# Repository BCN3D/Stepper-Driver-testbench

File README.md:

# Stepper Driver Test Bench
Electronics Test Bench used for testing and callibrating the Stepper drivers for the BCN3D Sigma.
It's based on a Pogo bed system where the bottom board has the components and the other two boards serve as support for
the board to test (Stepper driver).

Basically it's made for callibrating the power of the DRV8825 based Stepper drivers used in the BCND3D Sigma and testing them out
with a real motor.

It uses capacitive touch sensor instead of mechanical switches as it will be used a lot...
We were inspired by the awesome tutorial by [Sparkfun](https://learn.sparkfun.com/tutorials/constant-innovation-in-quality-control?_ga=1.225836058.1496890805.1425539418)

##Code
Implements the [AccelStepper](http://www.airspayce.com/mikem/arduino/AccelStepper/) Library and [Capacitive Sensor Library](http://playground.arduino.cc/Main/CapacitiveSensor?from=Main.CapSense).

One button conmutes the 24 Volt in from the power supply to avoid shorts and the other button starts a motor routine to test
the motor.

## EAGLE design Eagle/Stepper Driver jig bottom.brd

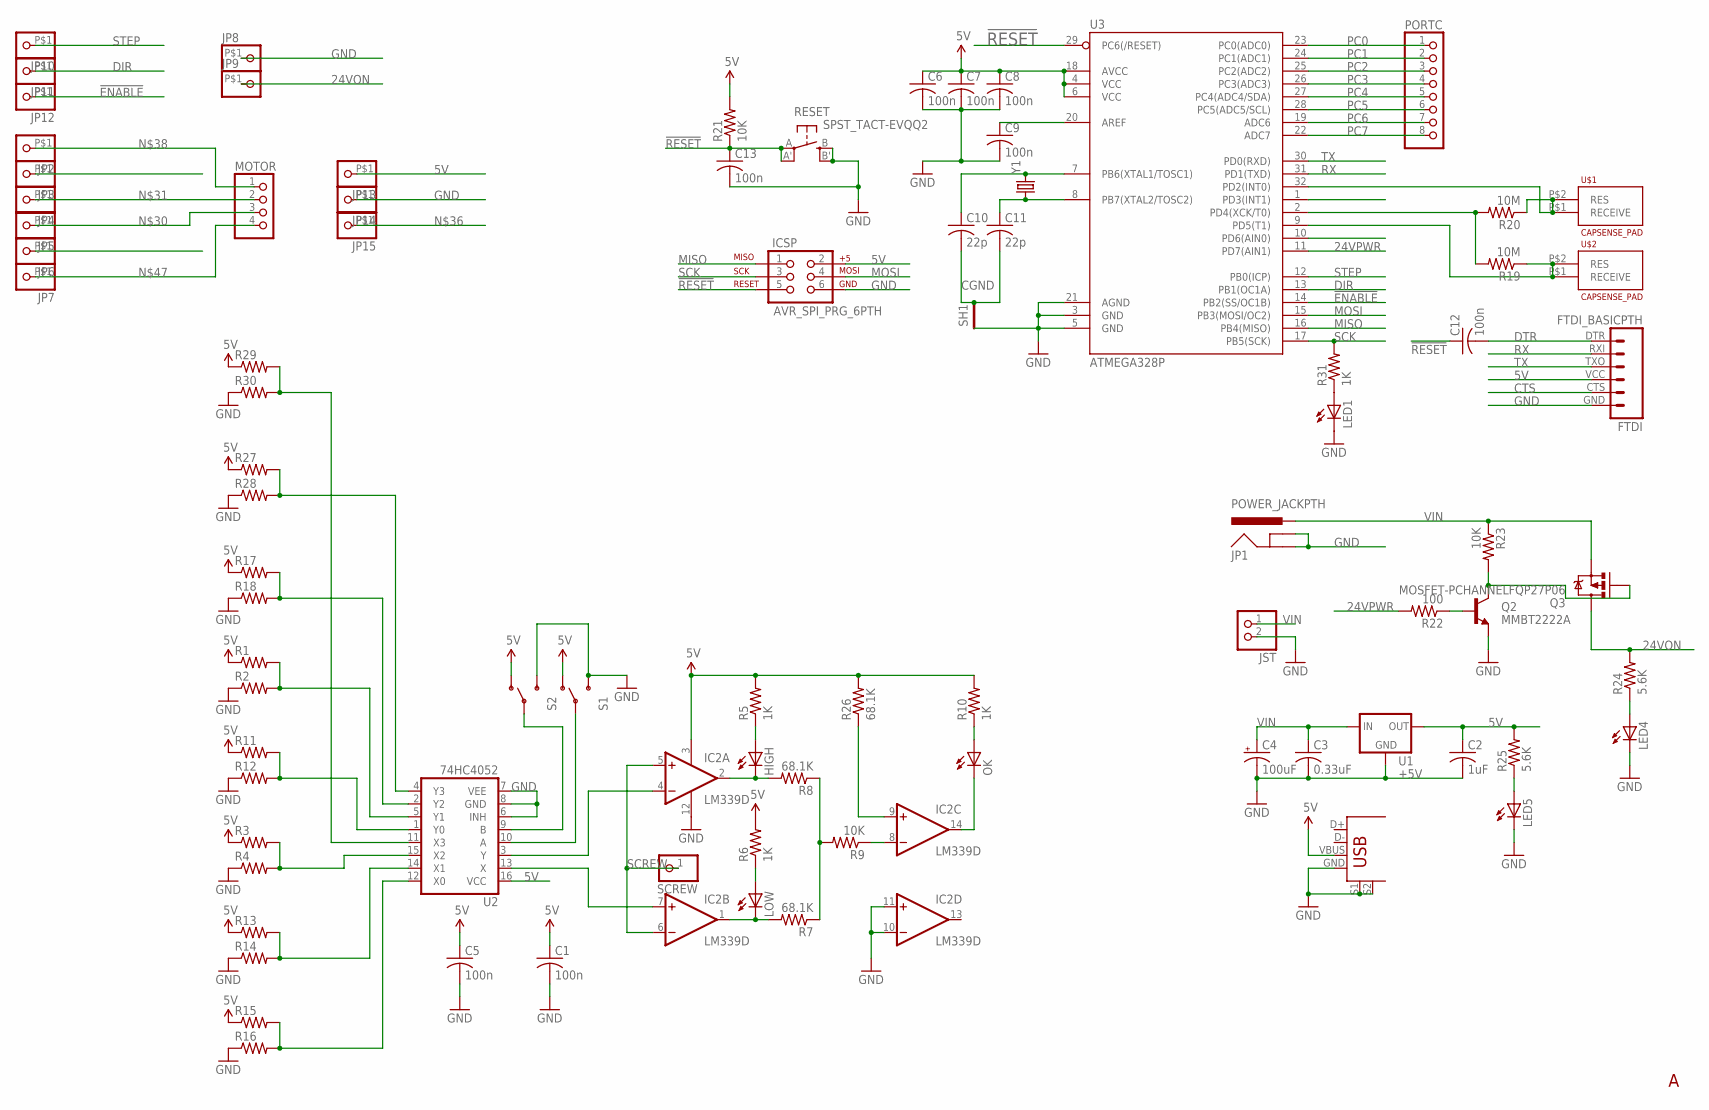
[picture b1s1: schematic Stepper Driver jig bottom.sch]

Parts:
C1, C5, C6, C7, C8, C9, C12, C13: 100n; C0805
C2: 1uF; C0805
C3: 0.33uF; C0805
C4: 100uF; UD-8X10_NICHICON
C10, C11: 22p; C0805
FTDI: FTDI_BASICPTH; FTDI_BASIC
HIGH: LEDCHIPLED_1206; CHIPLED_1206
IC2: LM339D; SO14
ICSP: AVR_SPI_PRG_6PTH; 2X3
JP1: POWER_JACKPTH; POWER_JACK_PTH
JP2, JP3, JP4, JP5, JP6, JP7, JP8, JP9, JP10, JP11, JP12, JP13, JP14, JP15: PINHD-1X1; POGOPIN
JST: JST_2PIN-SMT-RA; JST-PH-2-SMT-RA
LED1: LEDCHIP-LED0805; CHIP-LED0805
LED4, LED5: LEDCHIPLED_0805; CHIPLED_0805
LOW: LEDCHIPLED_1206; CHIPLED_1206
MOTOR: PINHD-1X4; 1X04
OK: LEDCHIPLED_1206; CHIPLED_1206
PORTC: PINHD-1X8; 1X08
Q2: MMBT2222A; SOT23-3
Q3: MOSFET-PCHANNELFQP27P06; TO220V
R1, R2, R3, R4, R11, R12, R13, R14, R15, R16, R17, R18, R27, R28, R29, R30: R-US_M0805; M0805
R5, R6, R10, R31: 1K; M0805
R7, R8, R26: 68.1K; M0805
R9, R21, R23: 10K; M0805
R19, R20: 10M; M0805
R22: 100; M0805
R24, R25: 5.6K; M0805
RESET: SPST_TACT-EVQQ2; EVQ-Q2
S1, S2: SWITCH-SPDTKIT; SWITCH-SPDT_KIT
SCREW: PINHD-1X1; 1X01
SH1: SHORTT5; SHORT_TOP-50
U1: +5V; TO-252
U2: 74HC4052; SO16
U3: ATMEGA328P; TQFP32-08
U$1, U$2: CAPSENSE_PAD
U$3: USB+SHIELD; USB-B-PTH
Y1: CRYSTALHC49US; HC49US

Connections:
5V: C1.1, C2.1, C5.1, C6.1, C7.1, C8.1, FTDI.VCC (4), IC2.3 (V+), ICSP.2, JP13.P$1, R1.1, R3.1, R5.2, R6.2, R10.2, R11.1, R13.1, R15.1, R17.1, R21.2, R25.2, R26.2, R27.1, R29.1, S1.1 (O), S2.1 (O), U1.2 (OUT), U2.16 (VCC), U3.4 (VCC), U3.6 (VCC), U3.18 (AVCC), U$3.VBUS
24VON: JP9.P$1, Q3.2 (D), R24.2
24VPWR: R22.2, U3.11 (PD7(AIN1))
!ENABLE: JP12.P$1, U3.14 (PB2(SS/OC1B))
!RESET: C12.1, C13.1, ICSP.5, R21.1, RESET.A, RESET.A' (P1), U3.29 (PC6(/RESET))
CGND: C10.2, C11.2, SH1.2
CTS: FTDI.CTS (5)
DIR: JP11.P$1, U3.13 (PB1(OC1A))
DTR: C12.2, FTDI.DTR (1)
GND: C1.2, C2.2, C3.2, C4.-, C5.2, C6.2, C7.2, C8.2, C9.2, C13.2, FTDI.GND (6), IC2.10 (-IN), IC2.11 (+IN), IC2.12 (GND), ICSP.6, JP1.GND, JP1.GNDBREAK, JP8.P$1, JP14.P$1, JST.2 (1), LED1.C, LED4.C, LED5.C, Q2.2 (E), R2.1, R4.1, R12.1, R14.1, R16.1, R18.1, R28.1, R30.1, RESET.B (S), RESET.B' (S1), S1.3 (S), S2.3 (S), SH1.1, U1.3 (GND), U2.6 (INH), U2.7 (VEE), U2.8 (GND), U3.3 (GND), U3.5 (GND), U3.21 (AGND), U$3.GND, U$3.S1, U$3.S2
MISO: ICSP.1, U3.16 (PB4(MISO))
MOSI: ICSP.4, U3.15 (PB3(MOSI/OC2))
unnamed: IC2.4 (-IN), U2.3 (Y)
unnamed: IC2.7 (+IN), U2.13 (X)
unnamed: IC2.1 (OUT), LOW.C, R7.2
unnamed: LOW.A, R6.1
unnamed: HIGH.C, IC2.2 (OUT), R8.2
unnamed: HIGH.A, R5.1
unnamed: R7.1, R8.1, R9.2
unnamed: IC2.8 (-IN), R9.1
unnamed: OK.A, R10.1
unnamed: IC2.14 (OUT), OK.C
unnamed: R11.2, R12.2, U2.1 (Y0)
unnamed: R1.2, R2.2, U2.5 (Y1)
unnamed: R3.2, R4.2, U2.15 (X2)
unnamed: R13.2, R14.2, U2.14 (X1)
unnamed: R15.2, R16.2, U2.12 (X0)
unnamed: R17.2, R18.2, U2.2 (Y2)
unnamed: S1.2, U2.10 (A)
unnamed: S2.2, U2.9 (B)
unnamed: R19.1, U3.9 (PD5(T1)), U$2.P$1 (RECEIVE), U$2.P$2 (RES)
unnamed: C11.1, U3.8 (PB7(XTAL2/TOSC2)), Y1.1
unnamed: C9.1, U3.20 (AREF)
unnamed: C10.1, U3.7 (PB6(XTAL1/TOSC1)), Y1.2
unnamed: Q2.3 (C), Q3.1 (G), R23.2
unnamed: Q2.1 (B), R22.1
unnamed: R19.2, R20.2, U3.2 (PD4(XCK/T0))
unnamed: R20.1, U3.32 (PD2(INT0)), U$1.P$1 (RECEIVE), U$1.P$2 (RES)
unnamed: JP5.P$1, MOTOR.3
unnamed: JP4.P$1, MOTOR.2
unnamed: JP2.P$1, MOTOR.1
unnamed: LED4.A, R24.1
unnamed: LED5.A, R25.1
unnamed: JP7.P$1, MOTOR.4
unnamed: IC2.9 (+IN), R26.1
unnamed: R27.2, R28.2, U2.4 (Y3)
unnamed: R29.2, R30.2, U2.11 (X3)
unnamed: LED1.A, R31.1
PC0: PORTC.1, U3.23 (PC0(ADC0))
PC1: PORTC.2, U3.24 (PC1(ADC1))
PC2: PORTC.3, U3.25 (PC2(ADC2))
PC3: PORTC.4, U3.26 (PC3(ADC3))
PC4: PORTC.5, U3.27 (PC4(ADC4/SDA))
PC5: PORTC.6, U3.28 (PC5(ADC5/SCL))
PC6: PORTC.7, U3.19 (ADC6)
PC7: PORTC.8, U3.22 (ADC7)
RX: FTDI.RXI (2), U3.31 (PD1(TXD))
SCK: ICSP.3, R31.2, U3.17 (PB5(SCK))
SCREW: IC2.5 (+IN), IC2.6 (-IN), SCREW.1
STEP: JP10.P$1, U3.12 (PB0(ICP))
TX: FTDI.TXO (3), U3.30 (PD0(RXD))
VIN: C3.1, C4.+, JP1.PWR, JST.1 (2), Q3.3 (S), R23.1, U1.1 (IN)

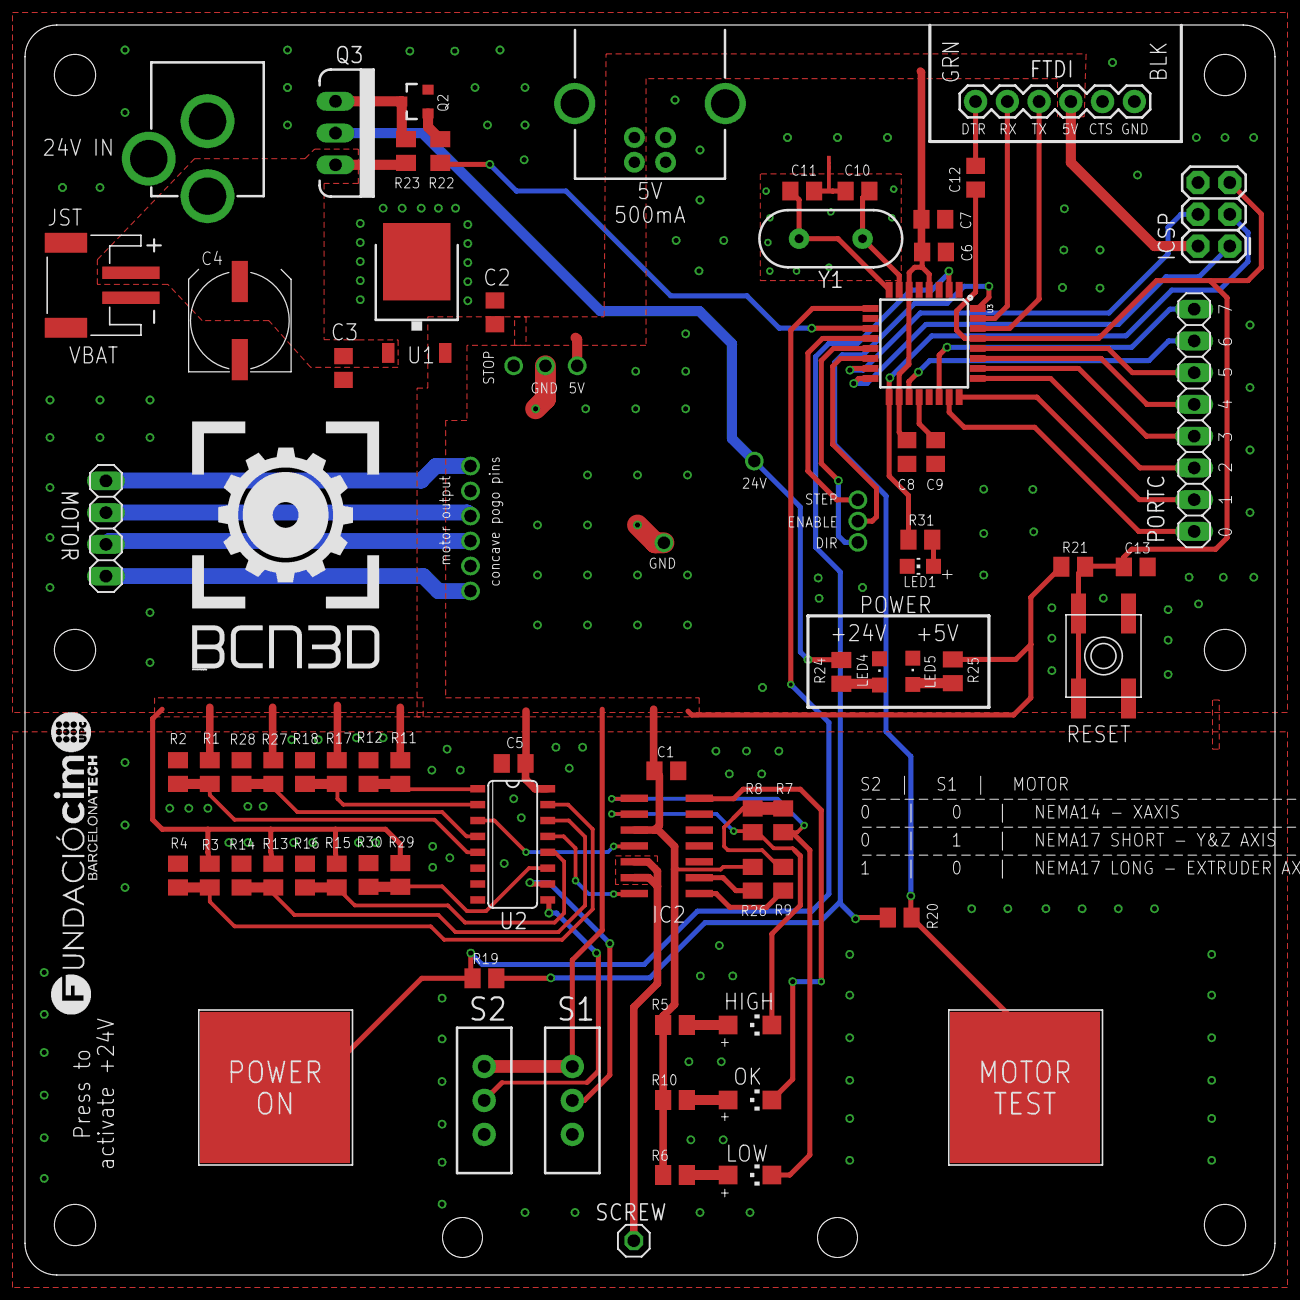
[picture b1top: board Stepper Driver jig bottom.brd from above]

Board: 2 copper layers, 100.0 x 100.0 mm, 93 parts (0 on the bottom side), 61 nets.

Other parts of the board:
U$4, U$5, U$6, U$7, U$8, U$9: STAND-OFF
U$10: FCIM_LOGO
U$11: BCN3D_LOGO

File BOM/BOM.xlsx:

Qty | Value | Device | Package | Parts | Description | BOM | PROD_ID | VALUE
1 |  | CRYSTALHC49US | HC49US | Y1 | Various standard crystals. Proven footprints.
1 |  | JST_2PIN-SMT-RA | JST-PH-2-SMT-RA | JST | JST 2-Pin Connectors of various flavors
1 |  | LEDCHIP-LED0805 | CHIP-LED0805 | LED1 | LED
2 |  | LEDCHIPLED_0805 | CHIPLED_0805 | LED4, LED5 | LED
3 |  | LEDCHIPLED_1206 | CHIPLED_1206 | HIGH, LOW, OK | LED
15 |  | PINHD-1X1 | 1X01 | SCREW, JP2, JP3, JP4, JP5, JP6, JP7, JP8, JP9, JP10, JP11, JP12, JP13, JP14, JP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 | Pin header 1x1 for 0.1 spacing"
1 |  | PINHD-1X4 | 1X04 | MOTOR | PIN HEADER
1 |  | PINHD-1X8 | 1X08 | PORTC | PIN HEADER
16 |  | R-US_M0805 | M0805 | R1, R2, R3, R4, R11, R12, R13, R14, R15, R16, R17, R18, R27, R28, R29, R30 | RESISTOR, American symbol
2 |  | SWITCH-SPDTKIT | SWITCH-SPDT_KIT | S1, S2 | SPDT Switch |  | SWCH-08261
1 | +5V | V_REG_78XX7812 | TO-252 | U1 | Voltage Regulator |  | VREG-12370 | +12v
1 | 0.33uF | C-USC0805 | C0805 | C3 | CAPACITOR, American symbol
1 | 100 | R-US_M0805 | M0805 | R22 | RESISTOR, American symbol
8 | 100n | C-USC0805 | C0805 | C1, C5, C6, C7, C8, C9, C12, C13 | CAPACITOR, American symbol
1 | 100uF | CPOL-USUD-8X10 | UD-8X10_NICHICON | C4 | POLARIZED CAPACITOR, American symbol
3 | 10K | R-US_M0805 | M0805 | R9, R21, R23 | RESISTOR, American symbol
2 | 10M | R-US_M0805 | M0805 | R19, R20 | RESISTOR, American symbol
4 | 1K | R-US_M0805 | M0805 | R5, R6, R10, R31 | RESISTOR, American symbol
1 | 1uF | C-USC0805 | C0805 | C2 | CAPACITOR, American symbol
2 | 22p | C-USC0805 | C0805 | C10, C11 | CAPACITOR, American symbol
2 | 5.6K | R-US_M0805 | M0805 | R24, R25 | RESISTOR, American symbol
3 | 68.1K | R-US_M0805 | M0805 | R7, R8, R26 | RESISTOR, American symbol
1 | 74HC4052 | 74HC4052SO | SO16 | U2 | Dual 4:1 analog mux |  | IC-09813 | 74HC4052
1 | ATMEGA328P | ATMEGA328P_TQFP | TQFP32-08 | U3 |  |  | IC-09069 | ATMEGA328P_TQFP
1 | AVR_SPI_PRG_6PTH | AVR_SPI_PRG_6PTH | 2X3 | ICSP | AVR ISP 6 Pin
2 | CAPSENSE_PAD | CAPSENSE_PAD | CAPSENSE_PAD | U$1, U$2 | Generic copper pad for a capacitive touch sensor.
1 | FTDI_BASICPTH | FTDI_BASICPTH | FTDI_BASIC | FTDI | FTDI Basic header with labels
1 | LM339D | LM339D | SO14 | IC2 | Low Power Low Offset Voltage Quad Comparators
1 | MMBT2222A | TRANSISTOR_NPNMMBT2222A | SOT23-3 | Q2 | Generic NPN BJT |  | TRANS-08049 | MMBT2222A
1 | MOSFET-PCHANNELFQP27P06 | MOSFET-PCHANNELFQP27P06 | TO220V | Q3 | Generic PMOSFET
1 | POWER_JACKPTH | POWER_JACKPTH | POWER_JACK_PTH | JP1 | Power Jack |  | CONN-08197
1 | SHORTT5 | SHORTT5 | SHORT_TOP-50 | SH1 | Short between two nets | no
1 | SPST_TACT-EVQQ2 | SPST_TACT-EVQQ2 | EVQ-Q2 | RESET | SMT 6mm switch, EVQQ2 series
1 | USB+SHIELD | USB+SHIELD | USB-B-PTH | U$3 | USB+Shield

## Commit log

2015-07-14 :boom::camel: Added .gitattributes
2015-07-14 First version of the Stepper driver test bench board
    All the documentation needed for replicating the Stepper driver test
    bench. Version 1.0 REV_A.
    Sent to Fab House
    I'll be uploading the code soon.
2015-07-16 Code Upload
    First version of the code. Not tested yet.
2015-07-24 Indicator LED function
    Now when you press a capacitive button, an led flashes for 5 ms to give
    some feedback.
2015-12-02 Reorder file tree
    new eagle folder

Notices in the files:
parts and their libraries:
SparkFun-DiscreteSemi: Licensing: Creative Commons ShareAlike 4.0 International - https://creativecommons.org/licenses/by-sa/4.0
